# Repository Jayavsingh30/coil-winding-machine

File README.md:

# coil-winding-machine
DIY automated coil winding machine with schematics, firmware, and documentation

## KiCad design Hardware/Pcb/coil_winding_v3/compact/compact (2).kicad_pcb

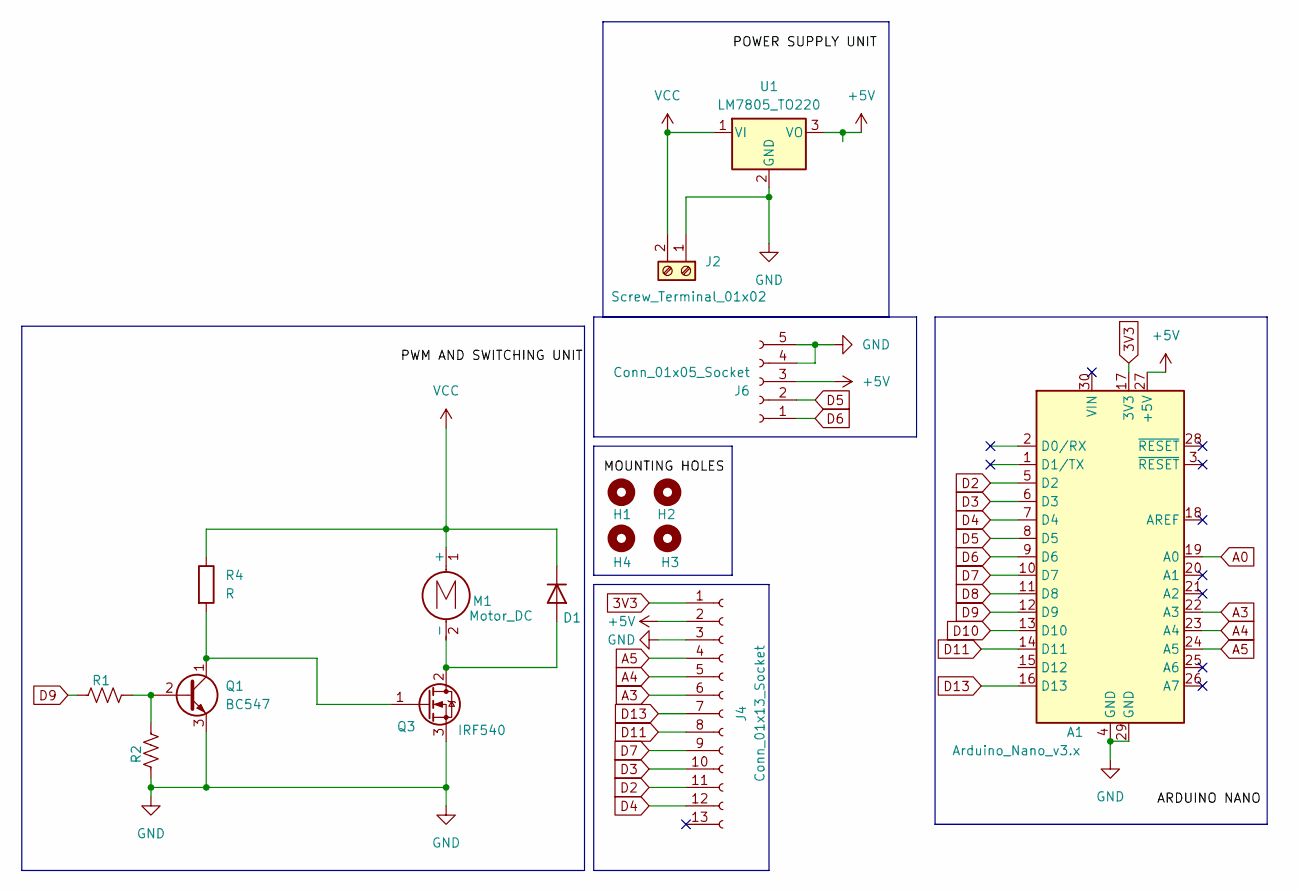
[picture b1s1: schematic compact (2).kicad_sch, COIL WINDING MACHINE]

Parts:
A1: Arduino_Nano_v3.x; Arduino_Nano
D1: D; D_DO-41_SOD81_P12.70mm_Horizontal
H1, H2, H3, H4: MountingHole; MountingHole_4mm
J2: Screw_Terminal_01x02; TerminalBlock_4Ucon_1x02_P3.50mm_Horizontal
J4: Conn_01x13_Socket; PinHeader_2x13_P2.54mm_Vertical
J6: Conn_01x05_Socket; PinHeader_2x05_P2.54mm_Vertical
M1: Motor_DC; TerminalBlock_4Ucon_1x02_P3.50mm_Horizontal
Q1: BC547; TO-92_Inline
Q3: IRF540; TO-220F-3_Vertical
R1: 220; R_Axial_DIN0207_L6.3mm_D2.5mm_P7.62mm_Horizontal
R2: 10K; R_Axial_DIN0207_L6.3mm_D2.5mm_P7.62mm_Horizontal
R4: R; R_Axial_DIN0207_L6.3mm_D2.5mm_P7.62mm_Horizontal
U1: LM7805_TO220; TO-220-3_Vertical

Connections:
3V3: A1.17 (3V3), J4.1
+5V: A1.27 (+5V), J4.2, J6.3, U1.3 (VO)
A0: A1.19 (A0)
A3: A1.22 (A3), J4.6
A4: A1.23 (A4), J4.5
A5: A1.24 (A5), J4.4
D2: A1.5 (D2), J4.11
D3: A1.6 (D3), J4.10
D4: A1.7 (D4), J4.12
D5: A1.8 (D5), J6.2
D6: A1.9 (D6), J6.1
D7: A1.10 (D7), J4.9
D8: A1.11 (D8)
D9: A1.12 (D9), R1.1
D10: A1.13 (D10)
D11: A1.14 (D11), J4.8
D13: A1.16 (D13), J4.7
GND: A1.4 (GND), A1.29 (GND), J2.1, J4.3, J6.4, J6.5, Q1.3 (E), Q3.3 (S), R2.1, U1.2 (GND)
unnamed: D1.2 (A), M1.2 (-), Q3.2 (D)
unnamed: Q1.2 (B), R1.2, R2.2
unnamed: Q1.1 (C), Q3.1 (G), R4.2

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
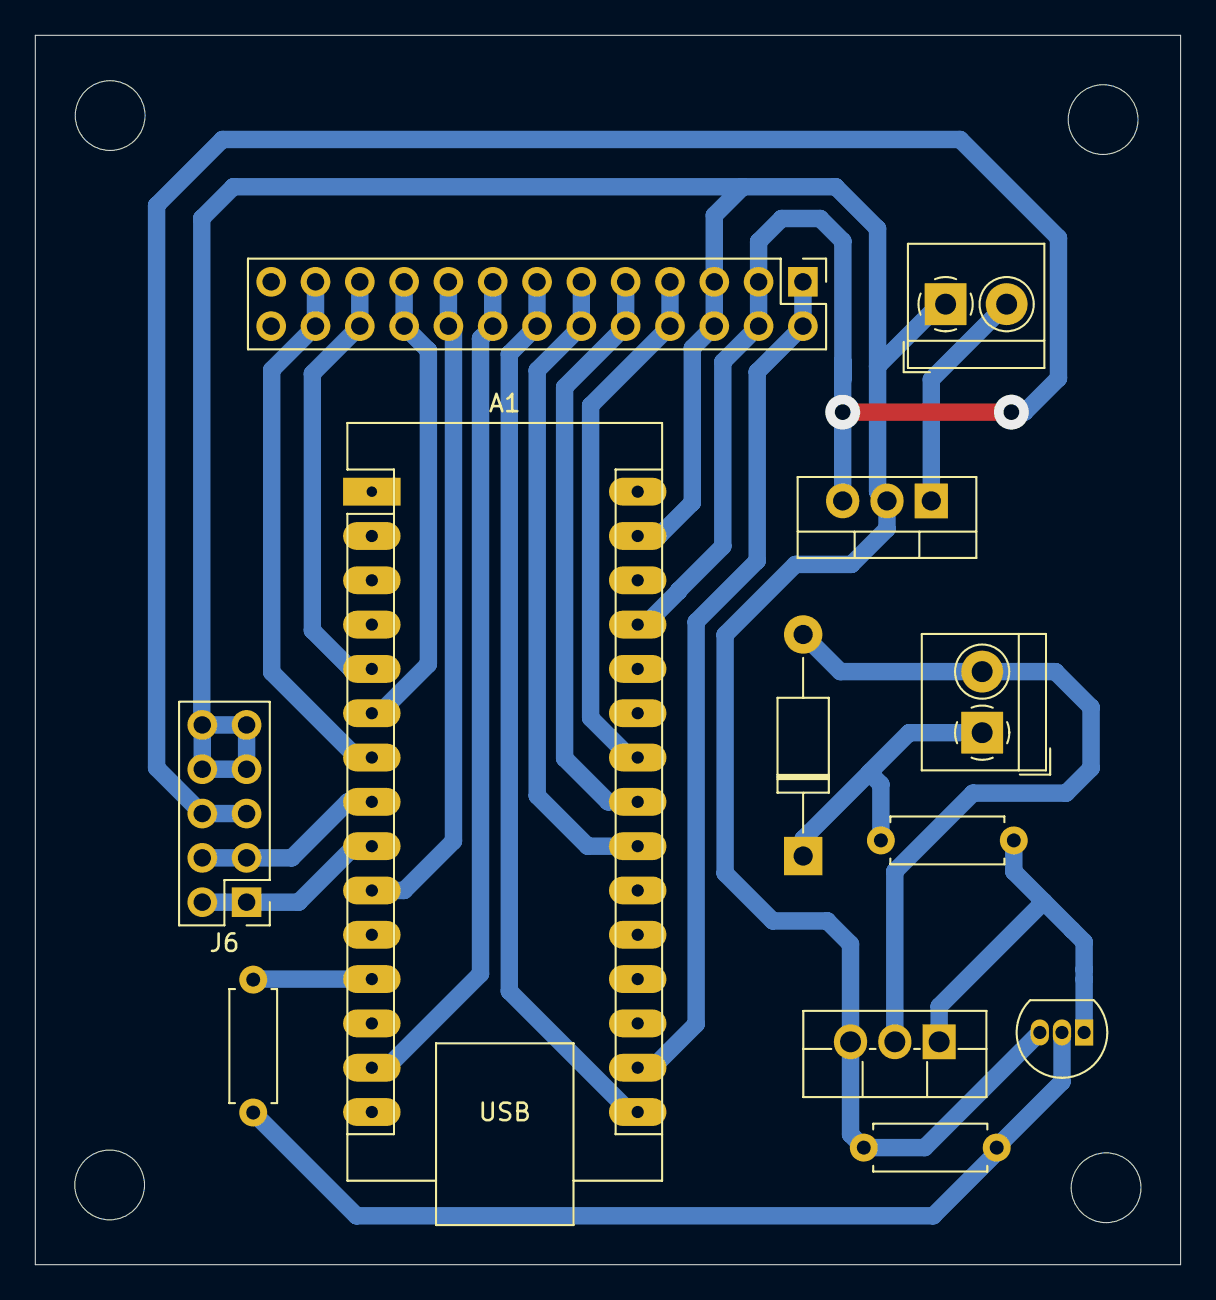
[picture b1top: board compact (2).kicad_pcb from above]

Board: 2 copper layers, 65.7 x 70.5 mm, 16 parts (0 on the bottom side), 20 nets.

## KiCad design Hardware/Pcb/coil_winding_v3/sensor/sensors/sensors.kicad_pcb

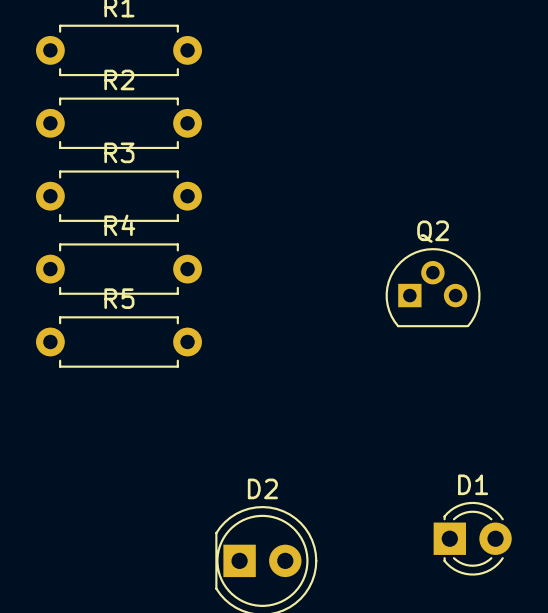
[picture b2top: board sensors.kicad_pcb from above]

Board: 2 copper layers, 12 parts (0 on the bottom side), 7 nets, no tracks yet.

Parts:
D1: LED; LED_D3.0mm_Clear
D2: LED; LED_D5.0mm
H1, H2, H3, H4: MountingHole; MountingHole_3.2mm_M3
Q2: BC547; TO-92L
R1: 150; R_Axial_DIN0207_L6.3mm_D2.5mm_P7.62mm_Horizontal
R2: 2.2k; R_Axial_DIN0207_L6.3mm_D2.5mm_P7.62mm_Horizontal
R3, R4: 4.7k; R_Axial_DIN0207_L6.3mm_D2.5mm_P7.62mm_Horizontal
R5: 1k; R_Axial_DIN0207_L6.3mm_D2.5mm_P7.62mm_Horizontal

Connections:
+5V: D1.2 (A), R1.1, R3.1, R5.1
DETECT: R3.2, R4.1
GND: Q2.3 (E), R2.2
unnamed: D1.1 (K), R2.1
unnamed: D2.2 (A), R5.2
unnamed: D2.1 (K), Q2.1 (C)
unnamed: Q2.2 (B), R4.2

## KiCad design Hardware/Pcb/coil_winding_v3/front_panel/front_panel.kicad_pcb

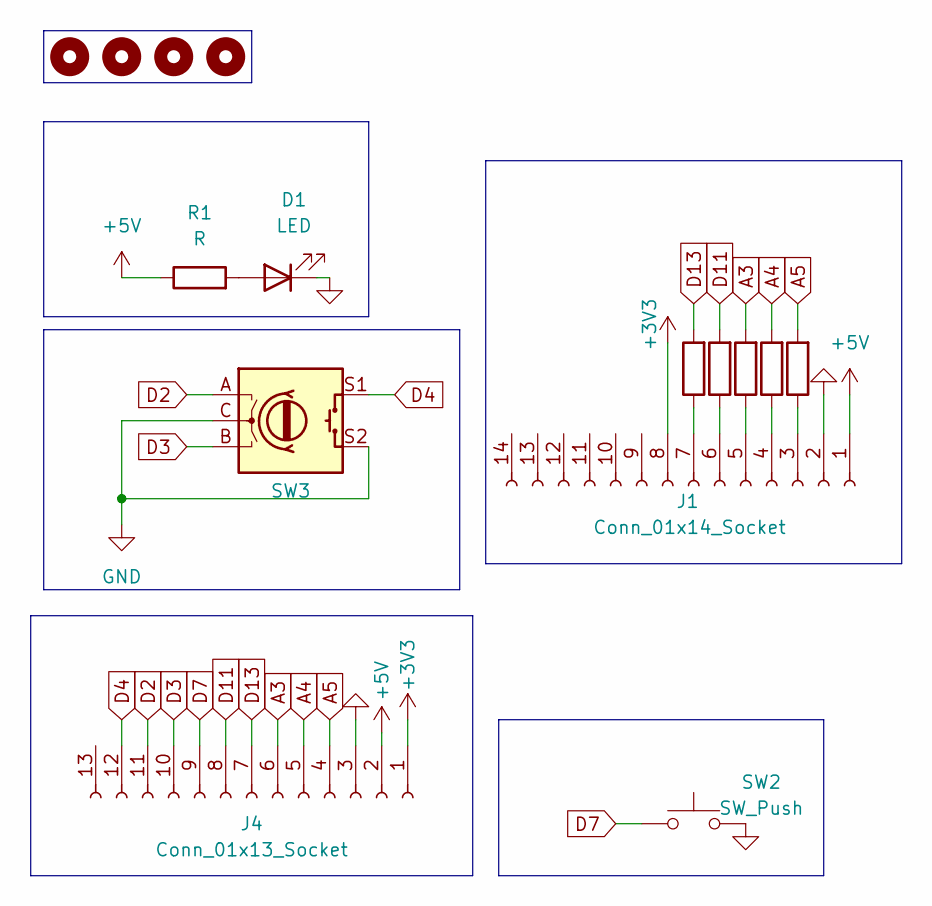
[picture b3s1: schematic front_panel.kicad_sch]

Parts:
D1: LED; LED_D5.0mm
H1, H2, H3, H4: MountingHole; MountingHole_3.2mm_M3
J1: Conn_01x14_Socket; PinSocket_1x14_P2.54mm_Vertical
J4: Conn_01x13_Socket; PinSocket_2x13_P2.54mm_Vertical
R1, R2, R3, R4, R6, R7: R; R_Axial_DIN0207_L6.3mm_D2.5mm_P7.62mm_Horizontal
SW2: SW_Push; SW_PUSH_6mm_H7.3mm
SW3: RotaryEncoder_Switch; RotaryEncoder_Alps_EC12E-Switch_Vertical_H20mm_CircularMoun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

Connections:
+3V3: J1.8, J4.1
+5V: J1.1, J4.2, R1.1
A3: J4.6, R4.2
A4: J4.5, R3.2
A5: J4.4, R2.2
D2: J4.11, SW3.A
D3: J4.10, SW3.B
D4: J4.12, SW3.S1
D7: J4.9, SW2.1
D11: J4.8, R7.2
D13: J4.7, R6.2
GND: D1.1 (K), J1.2, J4.3, SW2.2, SW3.C, SW3.S2
unnamed: D1.2 (A), R1.2
unnamed: J1.3, R2.1
unnamed: J1.4, R3.1
unnamed: J1.5, R4.1
unnamed: J1.6, R7.1
unnamed: J1.7, R6.1

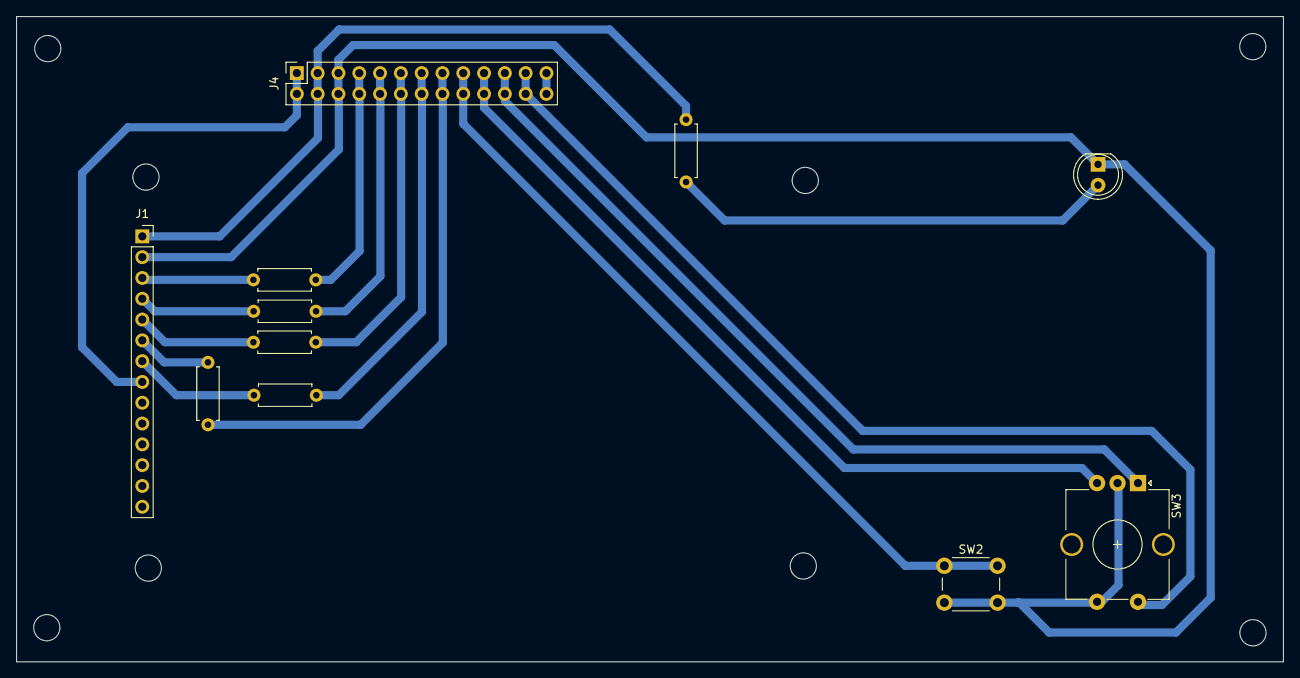
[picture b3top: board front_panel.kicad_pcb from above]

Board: 2 copper layers, 154.7 x 78.8 mm, 19 parts (0 on the bottom side), 18 nets.

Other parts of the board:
H1#2, H1#3, H1#4, H1#5: MountingHole; MountingHole_3.2mm_M3

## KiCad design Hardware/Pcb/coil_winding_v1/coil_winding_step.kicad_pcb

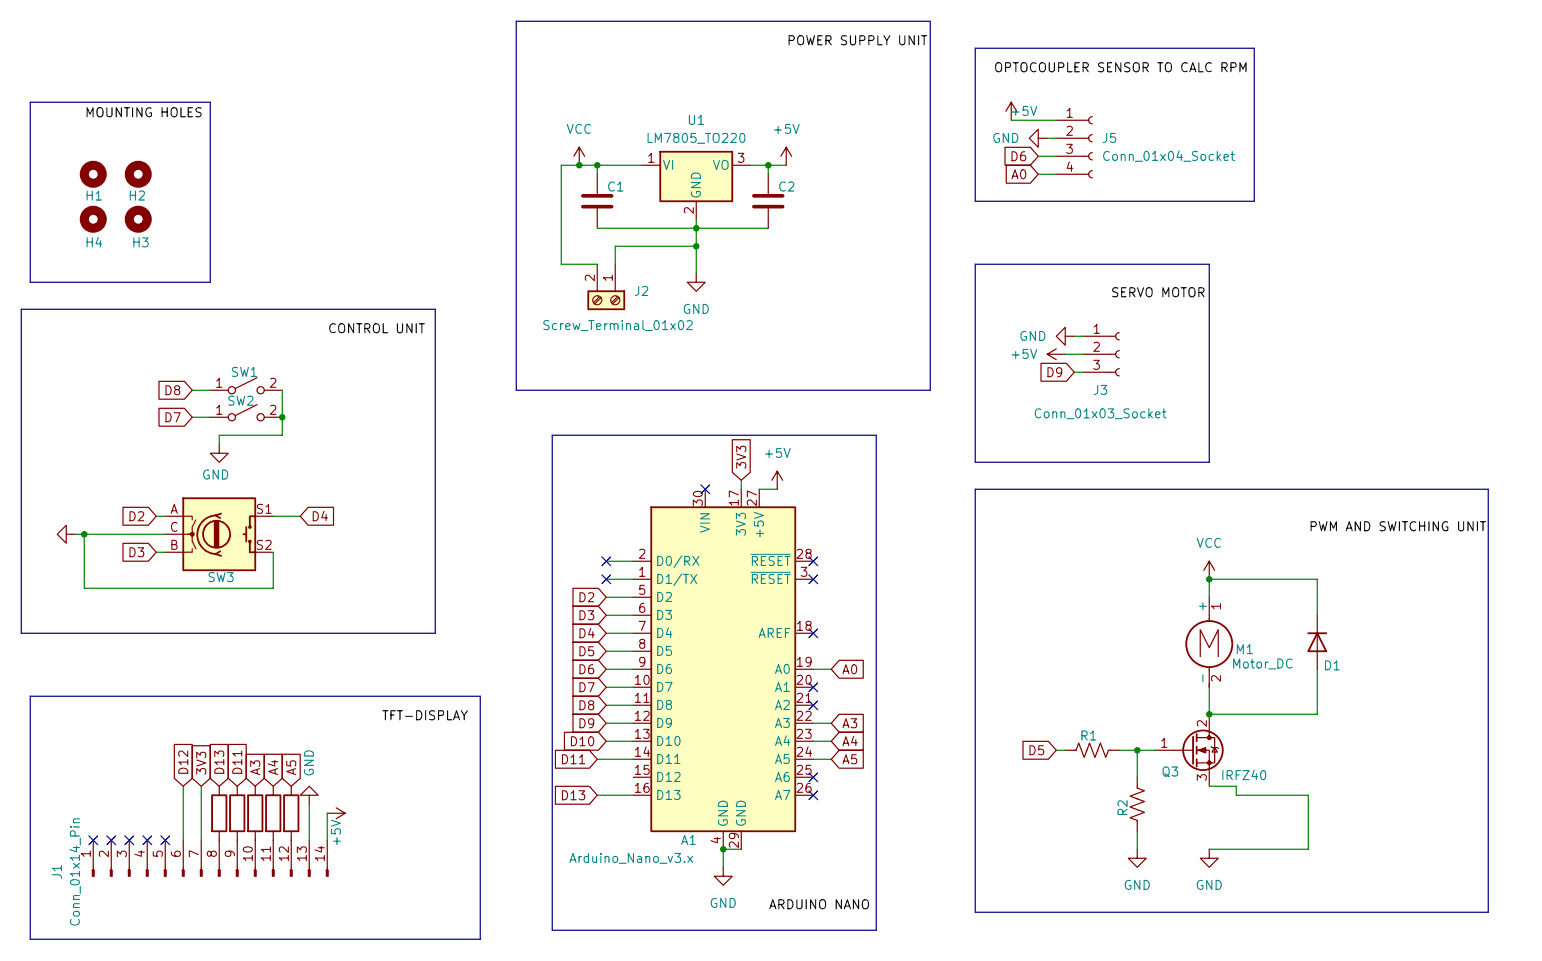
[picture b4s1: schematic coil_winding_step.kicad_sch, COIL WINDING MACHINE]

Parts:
A1: Arduino_Nano_v3.x; Arduino_Nano
C1, C2: C; CP_Radial_D5.0mm_P2.00mm
D1: D; D_DO-41_SOD81_P12.70mm_Horizontal
H1, H2, H3, H4: MountingHole; MountingHole_4mm
J1: Conn_01x14_Pin; PinSocket_1x14_P2.54mm_Vertical
J2: Screw_Terminal_01x02; BarrelJack_Horizontal
J3: Conn_01x03_Socket; PinSocket_1x03_P2.54mm_Vertical
J5: Conn_01x04_Socket; PinHeader_1x04_P2.54mm_Vertical
M1: Motor_DC; PinHeader_1x02_P2.54mm_Vertical
Q3: IRFZ40; TO-220F-3_Vertical
R1: 220; R_Axial_DIN0207_L6.3mm_D2.5mm_P7.62mm_Horizontal
R2: 10K; R_Axial_DIN0207_L6.3mm_D2.5mm_P7.62mm_Horizontal
R9, R10, R11, R12, R13: R; R_Axial_DIN0207_L6.3mm_D2.5mm_P7.62mm_Horizontal
SW1, SW2: SW_SPST; SW_PUSH_6mm_H7.3mm
SW3: RotaryEncoder_Switch; RotaryEncoder_Alps_EC12E-Switch_Vertical_H20mm
U1: LM7805_TO220; TO-220-3_Vertical

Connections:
3V3: A1.17 (3V3), J1.7
+5V: A1.27 (+5V), C2.1, J1.14, J3.2, J5.1, U1.3 (VO)
A0: A1.19 (A0), J5.4
A3: A1.22 (A3), R11.1
A4: A1.23 (A4), R10.1
A5: A1.24 (A5), R9.1
D2: A1.5 (D2), SW3.A
D3: A1.6 (D3), SW3.B
D4: A1.7 (D4), SW3.S1
D5: A1.8 (D5), R1.1
D6: A1.9 (D6), J5.3
D7: A1.10 (D7), SW2.1 (A)
D8: A1.11 (D8), SW1.1 (A)
D9: A1.12 (D9), J3.3
D10: A1.13 (D10)
D11: A1.14 (D11), R12.1
D12: J1.6
D13: A1.16 (D13), R13.1
GND: A1.4 (GND), A1.29 (GND), C1.2, C2.2, J1.13, J2.1, J3.1, J5.2, Q3.3 (S), R2.1, SW1.2 (B), SW2.2 (B), SW3.C, SW3.S2, U1.2 (GND)
unnamed: D1.2 (A), M1.2 (-), Q3.2 (D)
unnamed: J1.8, R13.2
unnamed: J1.9, R12.2
unnamed: J1.10, R11.2
unnamed: J1.11, R10.2
unnamed: J1.12, R9.2
unnamed: Q3.1 (G), R1.2, R2.2
VCC: C1.1, D1.1 (K), J2.2, M1.1 (+), U1.1 (VI)

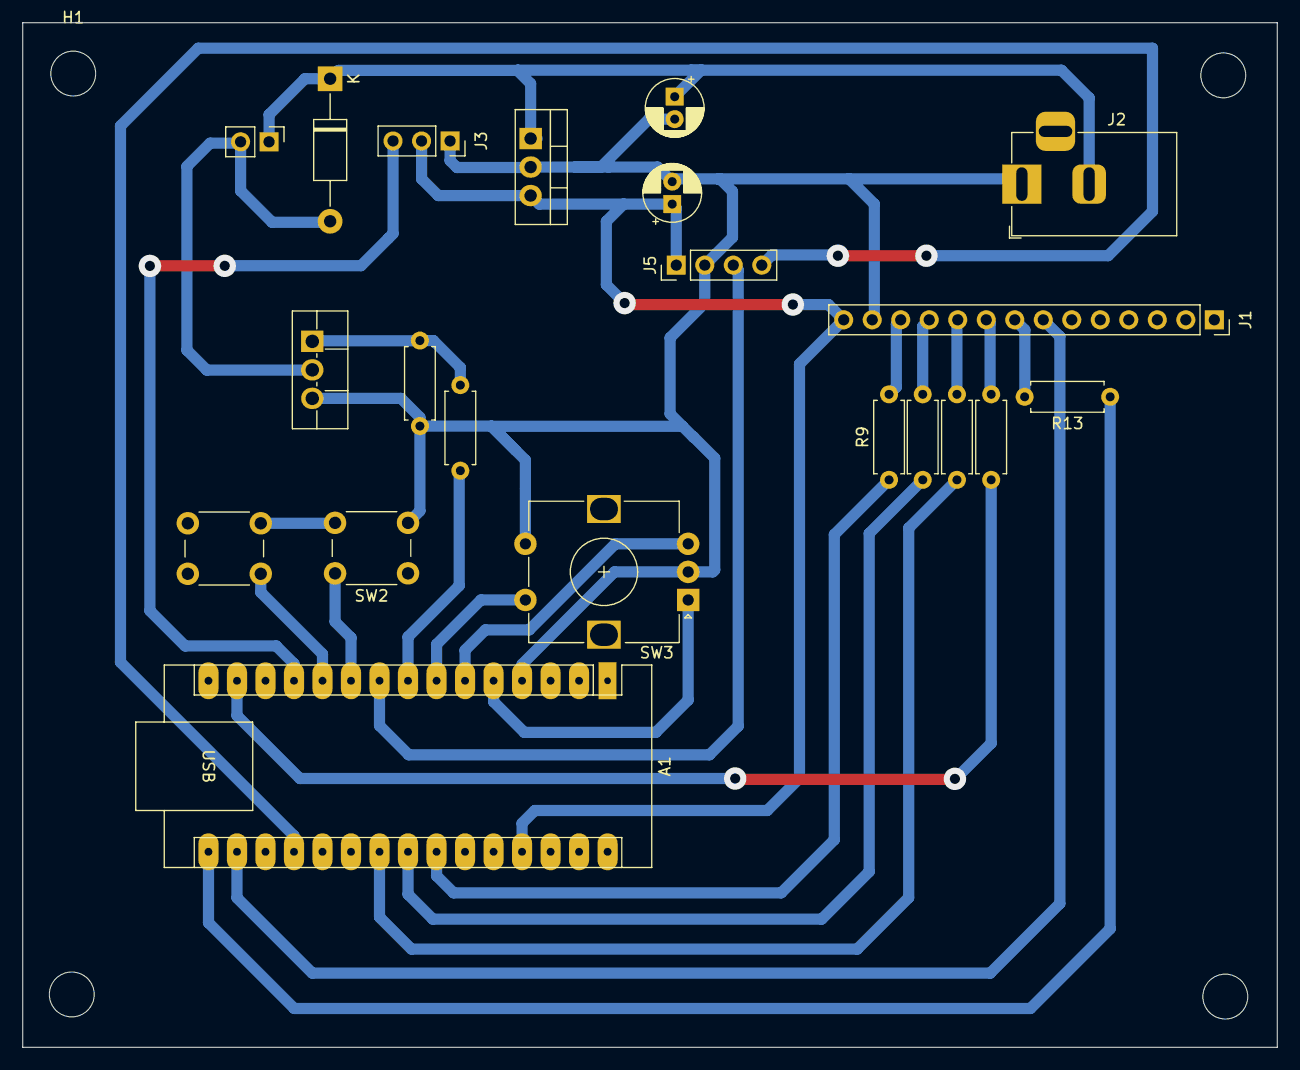
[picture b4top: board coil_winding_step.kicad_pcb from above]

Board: 2 copper layers, 111.8 x 91.3 mm, 25 parts (0 on the bottom side), 25 nets.

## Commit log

2025-05-22 Add KiCAD PCB project
2025-05-22 Update version-2 PCB: modified tracks and footprint
2025-05-23 Changes made
2025-05-24 Code for hardware
2025-05-24 updated_ui_code
2025-05-26 slight changes
2025-06-04 tuesday
2025-06-27 final_code
